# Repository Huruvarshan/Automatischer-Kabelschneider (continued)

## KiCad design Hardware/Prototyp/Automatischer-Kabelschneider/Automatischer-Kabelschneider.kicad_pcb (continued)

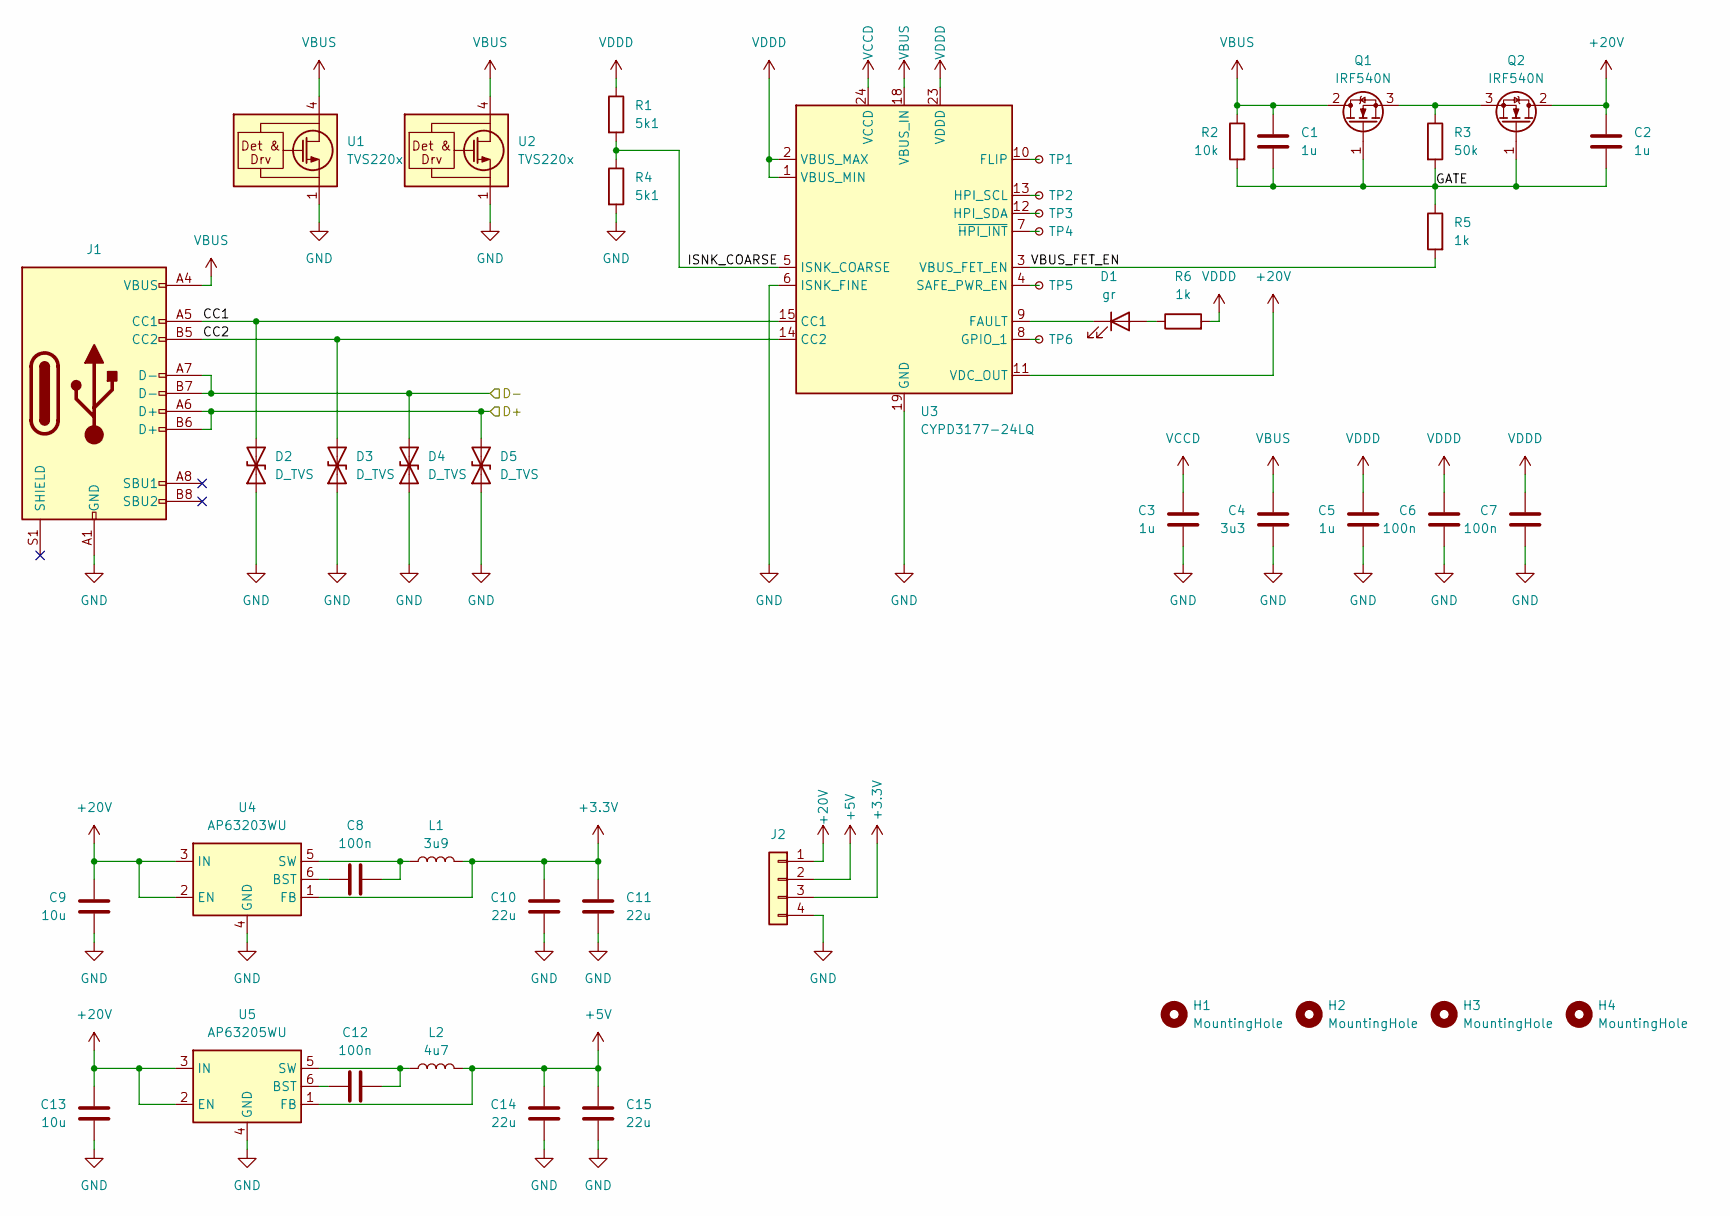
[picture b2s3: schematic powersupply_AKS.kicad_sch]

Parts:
C1, C2, C3, C5: 1u; C_0805_2012Metric
C4: 3u3; C_0805_2012Metric
C6, C7, C8, C12: 100n; C_0805_2012Metric
C9, C13: 10u; C_0805_2012Metric
C10, C11, C14, C15: 22u; C_0805_2012Metric
D1: gr; D_0805_2012Metric
D2, D3, D4, D5: D_TVS; D_0603_1608Metric
H1, H2, H3, H4: MountingHole; MountingHole_3.2mm_M3
J1: USB_C_Receptacle_USB2.0_16P; USB_C_Receptacle_GCT_USB4105-xx-A_16P_TopMnt_Horizontal
J2: Conn_01x04; PhoenixContact_GMSTBA_2,5_4-G-7,62_1x04_P7.62mm_Horizontal
L1: 3u9; L_Wurth_WE-LQSH-4020
L2: 4u7; L_Wurth_WE-LQSH-4020
Q1, Q2: IRF540N; TO-220-3_Vertical
R1, R4: 5k1; R_0805_2012Metric
R2: 10k; R_0805_2012Metric
R3: 50k; R_0805_2012Metric
R5, R6: 1k; R_0805_2012Metric
TP1, TP2, TP3, TP4, TP5, TP6: TestPoint_Small; TestPoint_Pad_D1.0mm
U1, U2: TVS220x; WSON-6-1EP_2x2mm_P0.65mm_EP1x1.6mm
U3: CYPD3177-24LQ; QFN-24-1EP_4x4mm_P0.5mm_EP2.75x2.75mm
U4: AP63203WU; TSOT-23-6
U5: AP63205WU; TSOT-23-6

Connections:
+3.3V: C10.1, C11.1, J2.3, L1.2, U4.1 (FB); also elsewhere on the board
+5V: C14.1, C15.1, J2.2, L2.2, U5.1 (FB); also elsewhere on the board
+20V: C2.1, C9.1, C13.1, J2.1, Q2.2 (D), U3.11 (VDC_OUT), U4.2 (EN), U4.3 (IN), U5.2 (EN), U5.3 (IN); also elsewhere on the board
/Main Microcontroller/D+: D5.2 (A2), J1.A6 (D+), J1.B6 (D+); also elsewhere on the board
/Main Microcontroller/D-: D4.2 (A2), J1.A7 (D-), J1.B7 (D-); also elsewhere on the board
/Powersupply_AKS/CC1: D2.2 (A2), J1.A5 (CC1), U3.15 (CC1)
/Powersupply_AKS/CC2: D3.2 (A2), J1.B5 (CC2), U3.14 (CC2)
/Powersupply_AKS/GATE: C1.2, C2.2, Q1.1 (G), Q2.1 (G), R2.2, R3.2, R5.1
/Powersupply_AKS/ISNK_COARSE: R1.2, R4.1, U3.5 (ISNK_COARSE)
/Powersupply_AKS/VBUS_FET_EN: R5.2, U3.3 (VBUS_FET_EN)
GND: C3.2, C4.2, C5.2, C6.2, C7.2, C9.2, C10.2, C11.2, C13.2, C14.2, C15.2, D2.1 (A1), D3.1 (A1), D4.1 (A1), D5.1 (A1), J1.A1 (GND), J1.A12 (GND), J1.B1 (GND), J1.B12 (GND), J2.4, R4.2, U1.1 (GND), U1.2 (GND), U1.3 (GND), U1.7 (GND), U2.1 (GND), U2.2 (GND), U2.3 (GND), U2.7 (GND), U3.6 (ISNK_FINE), U3.19 (GND), U3.22 (GND), U3.25 (GND), U4.4 (GND), U5.4 (GND); also elsewhere on the board
unnamed: D1.2 (A), R6.1
unnamed: D1.1 (K), U3.9 (FAULT)
unnamed: Q1.3 (S), Q2.3 (S), R3.1
unnamed: TP1.1, U3.10 (FLIP)
unnamed: TP6.1, U3.8 (GPIO_1)
unnamed: TP2.1, U3.13 (HPI_SCL)
unnamed: TP3.1, U3.12 (HPI_SDA)
unnamed: TP5.1, U3.4 (SAFE_PWR_EN)
unnamed: TP4.1, U3.7 (~HPI_INT)
unnamed: C8.2, U4.6 (BST)
unnamed: C8.1, L1.1, U4.5 (SW)
unnamed: C12.2, U5.6 (BST)
unnamed: C12.1, L2.1, U5.5 (SW)
VBUS: C1.1, C4.1, J1.A4 (VBUS), J1.A9 (VBUS), J1.B4 (VBUS), J1.B9 (VBUS), Q1.2 (D), R2.1, U1.4 (IN), U1.5 (IN), U1.6 (IN), U2.4 (IN), U2.5 (IN), U2.6 (IN), U3.18 (VBUS_IN)
VCCD: C3.1, U3.24 (VCCD)
VDDD: C5.1, C6.1, C7.1, R1.1, R6.2, U3.1 (VBUS_MIN), U3.2 (VBUS_MAX), U3.23 (VDDD)

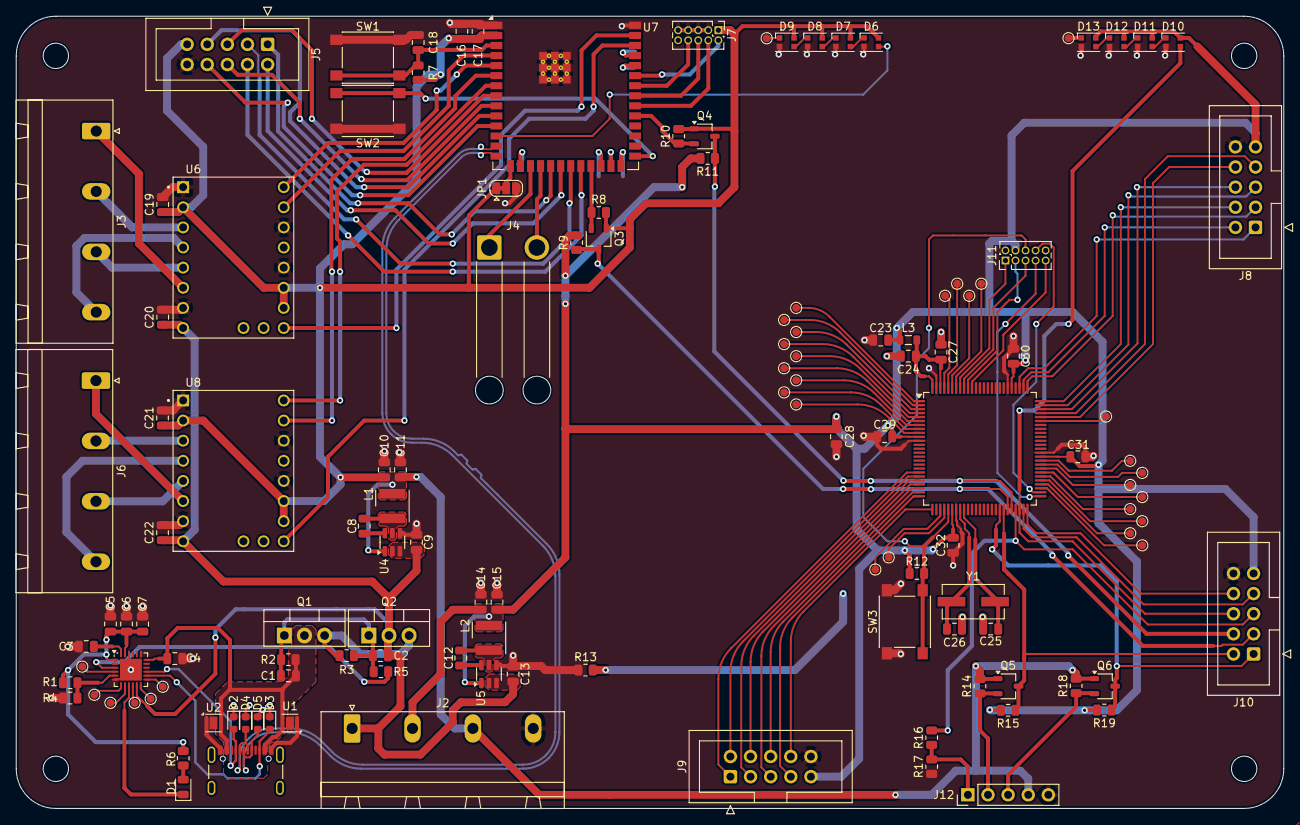
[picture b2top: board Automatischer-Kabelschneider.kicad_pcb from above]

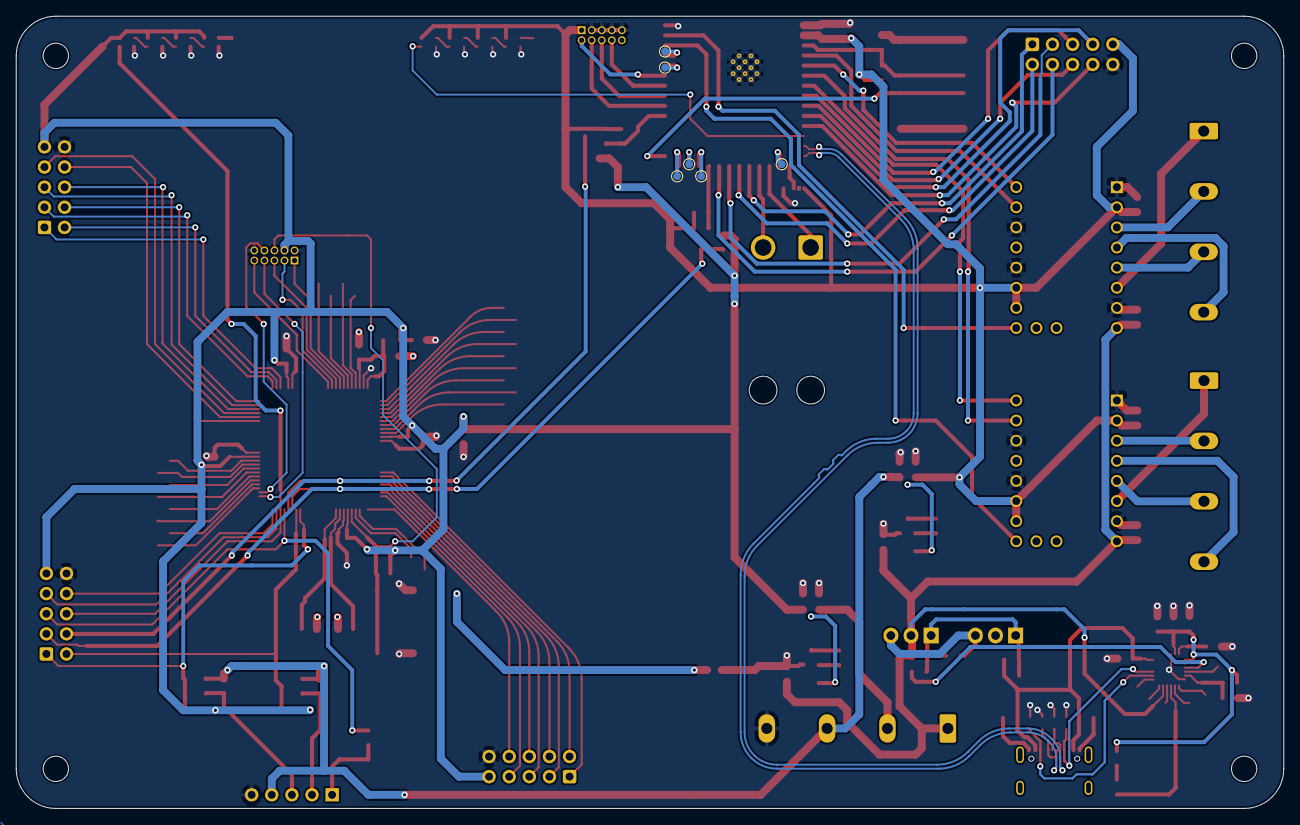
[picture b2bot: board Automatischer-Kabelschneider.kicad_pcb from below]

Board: 4 copper layers, 160.0 x 100.0 mm, 141 parts (6 on the bottom side), 137 nets.

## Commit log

2024-03-07 New folders
2024-03-27 Creation of prototype kicad project
2024-04-10 20240410
2024-04-11 20240411
2024-04-15 20240415
2024-04-19 20240418
2024-05-01 20240501
2024-05-09 Schematic completed
2024-05-12 PCB finished
2024-05-13 PCB no errors
2024-05-15 Prototype PCB finished
2024-06-05 Changed Q1 & Q2 from NMOS to PMOS
2024-07-06 First BUILD/FLASH on ESP32
2024-07-06 "BlinK" on IO17
2024-07-19 20240719
2024-07-21 Changeed to C6
2024-08-22 Stepper motor example
2024-08-30 Failed Switchreadall attempt
2024-09-10 Stepper motor working
2024-09-10 Trying out with stepper motor
2024-10-10 Something
2024-10-22 FreeRTOS tasks
2024-11-12 Able to now set length
2025-01-14 ESP-NOW ready to send
2025-01-21 Fuunctioning send command
2025-01-28 Semaphore basics
2025-03-25 before new code
2025-03-25 built aks program
2025-03-25 basic aks code
2025-03-31 Restructruring files
2025-03-31 Created V1
2025-04-08 Schematic v1.0 finished
2025-04-14 finished pcb v1.0
2025-04-15 Gerber created
2025-05-06 board v1.0 working with bugs
2025-05-06 new driver not working
2025-05-06 Revert "new driver not working"
    This reverts commit 447b560f67356a10be4f2f63d8f4024c33897fc5.
2025-05-06 New driver working bad
    turns motor, but wrong speed and steps. Also doesn't block motor.
2025-05-07 Old driver reimplemented
2025-05-07 20250507
2025-05-07 added step for board
2025-05-09 Touch input tested
2025-05-10 202050510 comms working
2025-05-12 Version working without led
2025-05-12 final before show
2025-05-18 Verissage
2025-05-20 deleted build
2025-05-20 Stuff added
2025-05-20 photos
2025-05-27 Added Arduino
